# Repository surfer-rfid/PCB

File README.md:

# PCB
PCB schematics, layout, BOM, and other data required to generate the S.U.R.F.E.R. PCB.
Note that one will see "rfidr" in many places in the source code. This is short
for "RFID reader", before S.U.R.F.E.R. had a unique name.

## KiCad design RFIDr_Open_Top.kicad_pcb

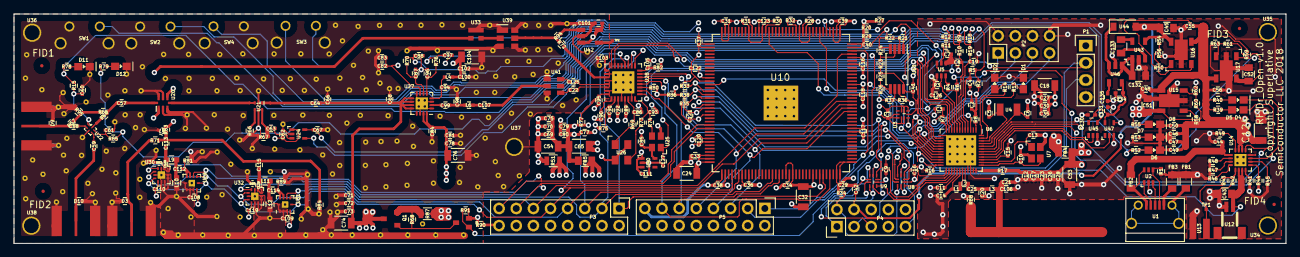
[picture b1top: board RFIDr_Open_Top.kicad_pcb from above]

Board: 4 copper layers, 188.5 x 34.0 mm, 522 parts (0 on the bottom side), 190 nets.

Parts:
C1, C2, C3, C4, C7, C8, C9, C15, C16, C17, C19, C26, C27, C29, C31, C34, C36, C38, C39, C40, C41, C42, C46, C47, C49, C50, C62, C89, C90, C92, C101, C103, C108, C109, C110, C116, C117, C118, C119, C120, C121, C122, C123, C130, C131: 100n; C_0402
C5, C6, C10, C13, C68, C86, C93: 12p; C_0402
C11: 47n; C_0402
C12, C23, C30, C33, C72, C75, C77, C78, C83, C102, C126: 1n; C_0402
C14: 2.2n; C_0402
C18, C24, C32, C53, C54, C65, C74, C76, C104, C124: 10u; C_1206
C20: 0.8p; C_0402
C21: 1.5p; C_0402
C22, C28, C35, C37, C57, C58, C59, C63, C64, C71, C79, C80, C81, C82, C100, C107, C125: 100p; C_0402
C25, C98: 2.2p; C_0402
C43, C45, C51, C52, C132, C133: 4.7u; C_0805
C44, C48, C55, C56, C85, C91, C95, C105, C111, C134: 1u; C_0402
C60, C61: 33p; C_0402
C66: 6.8p; C_0402
C67, C127: DNI; C_0402
C69, C70, C73, C135: 10n; C_0402
C84, C87, C88, C96, C97: DNP; C_0402
C94: 4.7p; C_0402
C99: 18p; C_0402
C106: 1.2p; C_0402
C112, C114: 5.2p; C_0402
C113: 15p; C_0402
C115: 20p; C_0402
C128, C129: 22p; C_0201
D1, D2, D7: LED_BLU; LED_0603
D3, D9, D10: XGD10402KR; R_0402
D4, D8, D12: LED_GRN; LED_0603
D5, D11: LED_YLW; LED_0603
D6: LED_RED; LED_0603
FB1, FB2, FB3, FB4, FB5: FERRITE; L_0805
FID1, FID2, FID3, FID4: FIDUCIAL; RFIDr_Fiducial_1mm_Dia_2.54mm_Outer_CopperTop
L1: 10n; L_0402
L2: 4.7n; L_0402
L3: 3.3n; L_0402
L4: 1n; L_0402
L5: 12n; L_0402
L6: 1.8n; L_0402
L9, L11: 3.6n; L_0603
L10, L12: 1.6n; L_0603
P1: CONN_01X04; Pin_Header_Straight_1x04
P2: CONN_02X04; Pin_Header_Straight_2x04
P3, P5: CONN_02X08; Pin_Header_Straight_2x08
P4: CONN_02X05; Pin_Header_Straight_2x05
Q1: DMP2305; SOT23
Q2: CTRL_NMOS; SOT-323
R1, R22, R37, R43, R59: DNP; R_0402
R2, R3, R5, R9, R10, R11, R12, R18, R19, R30, R31, R32, R33, R34, R35, R68, R81, R89, R91: 10k; R_0402
R4, R6: 2.2k; R_0402
R7, R8, R17, R20, R21, R27, R28, R29, R36, R41, R44, R45, R47, R50, R58, R64, R69, R70, R72, R73, R75, R76, R77, R80, R82, R86, R88, R90, R94, R95: 0; R_0402
R13, R14, R52, R53, R55: 220; R_0402
R15, R39, R40, R85: 470; R_0402
R16, R23, R25: 12k; R_0402
R24, R26: 100k; R_0402
R38: 1k; R_0402
R42: 15k; R_0402
R46: 1.13k; R_0402
R48: 46.8k; R_0402
R49: 1.1k; R_0402
R51, R87: 0; R_0805
R54: 82k; R_0402
R56: 36k; R_0402
R57, R65, R71, R74: DNI; R_0402
R60: 68k; R_0402
R61, R78, R79: 24k; R_0402
R62: 23k; R_0402
R63: 47k; R_0402
R66, R67: 50; R_0402
R83: 10; R_0402
R84: 19; R_0402
R92, R93: 10k; R_0201
SW1, SW3: SW_RESET; FSMRA3JH
SW2, SW4: SW_SAMPLE; FSMRA3JH
TP1, TP2: TESTPOINT
U1: USB_Micro_B; USB_Micro-B-Round-Pegs
U2: PUSB2X4Y; SC-70-6
U3, U8, U9: NLAS5223B; WQFN-10
U4: FC-135_32p768_XTAL; FC-135
U5: DMN63D8LDW-7; SC-70-6
U6: NRF51822; UQFN-48-1EP_6x6mm_Pitch0.4mm_wvias
U7: NX2520SA_16MHz_XTAL; NX2520
U10: 10M02E144; EQFP-144_20x20mm_Pitch0.5mm
U11: TSV358; TSSOP-8_4.4x3mm_Pitch0.65mm
U12: BatJSTCnctr; JST-SM-02B-SRSS-TB
U13: Thermocouple; THERMOCOUPLE
U14: BQ24073; QFN-16-1EP_3x3mm_Pitch0.5mm_wvias
U15, U16, U17: AP7361C-Y5-13; SOT-89-5
U18, U19, U23: SMA_72970
U20: J0910CF15B0100
U21: HHM22106
U22: SKY13350
U24: MAX2204; SC-70-5
U25: SG210STF_XO; SG210STF
U26: CX3225GB_36MHz_XTAL; CX3225
U27: SKY65111; QFN-16-1EP_3x3mm_Pitch0.5mm_wvias
U28: SX1257; QFN-32-1EP_5x5mm_Pitch0.5mm_wvias
U29, U31: PE64906; QFN-10-1EP_2x2mm_Pitch0.5mm_wvias
U30, U32: PE64102; QFN-12-1EP_2x2mm_Pitch0.5mm_wvias
U33: PAT1220
U34, U35, U36, U37, U38: MountingHole; MountingHole_2.2mm
U39: SF2049E
U40: LP5951MF; SC-70-5
U41: 0917BL18B100E
U42: LTC5505-1; TSOT-23-5
U43: LM2767M5; SOT-23-5
U44: MBR0520LTR
U45, U47: SN74LV1T34; SC-70-5
U46: LP3985IM5-5.0; SOT-23-5
V6, V7, V8, V9, V10, V11, V12, V14, V15, V16, V18, V19, V25, V35, V54, V105, V107, V108, V109, V110, V112, V113, V114, V115, V116, V117, V118, V119, V120, V121, V122, V124, V125, V126, V127, V128, V129, V130, V131, V132, V134, V135, V136, V137, V138, V139, V140, V141, V142, V143, V144, V145, V146, V147, V148, V149, V150, V151, V152, V153, V154, V155, V156, V157, V158, V159, V160, V161, V162, V163, V164, V165, V166, V167, V168, V169, V170, V171, V172, V173, V174, V175, V176, V177, V178, V179, V180, V181, V182, V183, V184, V185, V186, V187, V188, V189, V190, V191, V193, V194, V195, V196, V197, V198, V199, V200, V201, V202, V204, V205, V206, V207, V208, V209, V210, V211, V212, V213, V214, V215, V216, V217, V218, V219, V220, V221, V222, V223, V224, V225, V226, V227, V228, V229, V230, V231, V232, V234, V235, V236, V237, V312, V313, V314, V315, V316, V317, V318, V319, V320, V321, V322, V323, V324, V325, V326, V327, V328, V329, V330, V331, V332, V333, V334, V335, V336, V337, V338, V339, V340, V341, V342, V343, V344, V345, V346, V347, V348, V349, V350, V351, V357, V366, V367, V368, V369, V370, V371, V372, V373, V374, V375, V376, V377, V378, V379, V380, V381, V382, V383, V384: RF_VIA

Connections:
+1V2: C52.2, R61.2, U17.5
+2V5: C42.2, C45.2, P4.4, R54.2, U16.5, U43.4, U44.2
+5V: C130.1, C131.2, C134.1, U45.5, U46.5, U47.5
/ANT0: R15.1, R78.1, U47.4
/ANT1: R79.1, R85.2, U45.4
/CHGB: D4.1, U6.43, U14.9
/CTRLR_CIPO: P3.1, U10.54, U28.18
/CTRLR_COPI_CAP0_RDIO: P3.3, U10.52, U28.19, U32.12
/CTRLR_COPI_CAP1: P3.11, U10.105, U31.7
/CTRLR_COPI_CAP2: P3.15, U10.25, U30.12
/CTRLR_COPI_CAP3: P3.13, U10.26, U29.7
/CTRLR_NPS_DTC: P3.7, U10.40, U29.6, U30.1, U31.6, U32.1
/CTRLR_NPS_RDIO: P3.5, U10.42, U28.20
/CTRLR_PCLK: P3.9, U10.90, U28.17, U29.5, U30.3, U31.5, U32.3
/DIO2: U6.14, U28.23
/DIO3: U6.10, U28.24
/EN_VDD_1P2: R52.2, R59.1, U6.44, U17.1
/EN_VDD_PA: Q1.1, Q2.3, R68.2
/FPGA_CLK_36_IN: P5.9, U10.91, U28.10
/FPGA_IN_I: P5.5, U10.89, U28.15
/FPGA_IN_Q: P5.7, U10.88, U28.14
/FPGA_OUT_I: P5.11, U10.67, U28.13
/FPGA_OUT_Q: P5.13, U10.69, U28.12
/OPA_SPDT1_CTL: U3.8, U6.11, U24.4
/PGOODB: D5.1, U6.42, U14.7
/RDIO_RST_P: U6.15, U28.9
/RFIDr_Open_DigBB/CYCLE: R9.2, R10.2, SW4.2
/RFIDr_Open_DigBB/FPGA_IRQ: P5.1, U6.21, U10.106
/RFIDr_Open_DigBB/FPGA_PRPHL_CIPO: P2.5, U6.18, U10.115
/RFIDr_Open_DigBB/FPGA_PRPHL_COPI: P2.7, U6.17, U10.130
/RFIDr_Open_DigBB/FPGA_PRPHL_NPS: P2.3, U6.19, U10.13
/RFIDr_Open_DigBB/FPGA_PRPHL_PCLK: P2.1, U6.20, U10.113
/RFIDr_Open_DigBB/FPGA_RST_N: U6.22, U10.19
/RFIDr_Open_DigBB/FPGA_TCK_MCU: U6.28, U9.10
/RFIDr_Open_DigBB/FPGA_TDI_MCU: U6.26, U8.10
/RFIDr_Open_DigBB/FPGA_TDO_MCU: U6.25, U8.2
/RFIDr_Open_DigBB/FPGA_TMS_MCU: U6.27, U9.2
/RFIDr_Open_DigBB/PWR_TOGL: R2.2, R5.2, SW1.1
/RFIDr_Open_DigBB/RESET: R11.1, R12.1, SW3.2
/RFIDr_Open_DigBB/RFIDr_Open_FPGA/CONFIG_SEL: R28.2, U10.120
/RFIDr_Open_DigBB/RFIDr_Open_FPGA/CONF_DONE: R31.2, U10.135
/RFIDr_Open_DigBB/RFIDr_Open_FPGA/FPGA_TCK: R38.1, U9.9, U10.16
/RFIDr_Open_DigBB/RFIDr_Open_FPGA/FPGA_TDI: R35.2, U8.9, U10.17
/RFIDr_Open_DigBB/RFIDr_Open_FPGA/FPGA_TDO: U8.3, U10.18
/RFIDr_Open_DigBB/RFIDr_Open_FPGA/FPGA_TMS: R33.2, U9.3, U10.15
/RFIDr_Open_DigBB/RFIDr_Open_FPGA/JTAG_SEL: P4.2, R34.2, U8.4, U8.8, U9.4, U9.8
/RFIDr_Open_DigBB/RFIDr_Open_FPGA/JTAG_TCK: P4.1, U9.7
/RFIDr_Open_DigBB/RFIDr_Open_FPGA/JTAG_TDI: P4.9, U8.7
/RFIDr_Open_DigBB/RFIDr_Open_FPGA/JTAG_TDO: P4.3, U8.5
/RFIDr_Open_DigBB/RFIDr_Open_FPGA/JTAG_TMS: P4.5, U9.5
/RFIDr_Open_DigBB/RFIDr_Open_FPGA/NCONFIG: R32.2, U10.122
/RFIDr_Open_DigBB/RFIDr_Open_FPGA/NSTATUS: R30.2, U10.131
/RFIDr_Open_DigBB/RFIDr_Open_MCU/ADC_IN: R4.1, R6.2, U6.7
/RFIDr_Open_DigBB/RFIDr_Open_MCU/ANT0_3V: U6.40, U47.2
/RFIDr_Open_DigBB/RFIDr_Open_MCU/ANT1B: L1.1, L2.1, U6.31
/RFIDr_Open_DigBB/RFIDr_Open_MCU/ANT1_3V: U6.41, U45.2
/RFIDr_Open_DigBB/RFIDr_Open_MCU/ANT2B: C25.1, L2.2, U6.32
/RFIDr_Open_DigBB/RFIDr_Open_MCU/BAT_LED0: R14.2, U6.48
/RFIDr_Open_DigBB/RFIDr_Open_MCU/BAT_LED1: R13.2, U6.47
/RFIDr_Open_DigBB/RFIDr_Open_MCU/BAT_SENSE: R3.2, U5.2, U6.8
/RFIDr_Open_DigBB/RFIDr_Open_MCU/BTLE_DECOUPLE1: C15.1, U6.39
/RFIDr_Open_DigBB/RFIDr_Open_MCU/BTLE_DECOUPLE2: C11.1, U6.29
/RFIDr_Open_DigBB/RFIDr_Open_MCU/BTLE_SWCLK: P1.3, R16.2, U6.24
/RFIDr_Open_DigBB/RFIDr_Open_MCU/BTLE_SWDIO: P1.2, U5.6, U6.23
/RFIDr_Open_DigBB/RFIDr_Open_MCU/CYCLE_F: C8.2, R10.1, U6.6
/RFIDr_Open_DigBB/RFIDr_Open_MCU/LPXC1_BT: C6.1, U4.2, U6.45
/RFIDr_Open_DigBB/RFIDr_Open_MCU/LPXC2_BT: C5.1, U4.1, U6.46
/RFIDr_Open_DigBB/RFIDr_Open_MCU/PWR_TOGL_F: C4.2, R5.1, U6.4
/RFIDr_Open_DigBB/RFIDr_Open_MCU/RESET_F: C7.2, R11.2, U5.5
/RFIDr_Open_DigBB/RFIDr_Open_MCU/RFIDr_Open_BTLE_ANT/ANT: C21.1, C106.1, L3.2, R88.1
/RFIDr_Open_DigBB/RFIDr_Open_MCU/RFIDr_Open_PA_BIAS_CTRL/DAC_OA0: R23.1, R24.1, U11.3
/RFIDr_Open_DigBB/RFIDr_Open_MCU/RFIDr_Open_PA_BIAS_CTRL/DAC_OA0_FB: R21.1, R22.1, U11.2
/RFIDr_Open_DigBB/RFIDr_Open_MCU/RFIDr_Open_PA_BIAS_CTRL/DAC_OA1: R25.1, R26.1, U11.5
/RFIDr_Open_DigBB/RFIDr_Open_MCU/RFIDr_Open_PA_BIAS_CTRL/DAC_OA1_FB: R36.1, R37.1, U11.6
/RFIDr_Open_DigBB/RFIDr_Open_MCU/RFIDr_Open_PA_BIAS_CTRL/VDD_OPA_PA: C41.1, R23.2, R25.2, U3.9, U11.8
/RFIDr_Open_DigBB/RFIDr_Open_MCU/SAMPLE_F: C19.2, R19.1, U6.5
/RFIDr_Open_DigBB/RFIDr_Open_MCU/VDD_PA_BTLE: C14.1, L1.2, U6.30
/RFIDr_Open_DigBB/RFIDr_Open_MCU/XC1_BT: C10.1, U6.37, U7.3
/RFIDr_Open_DigBB/RFIDr_Open_MCU/XC2_BT: C13.1, U6.38, U7.1
/RFIDr_Open_DigBB/SAMPLE: R18.2, R19.2, SW2.1
/RFIDr_Open_PMU/ID: R1.2, U1.4, U2.4
/RFIDr_Open_PMU/RFIDr_Open_LDOS_QPUMP/CP_M: C133.2, U43.3
/RFIDr_Open_PMU/RFIDr_Open_LDOS_QPUMP/CP_P: C133.1, U43.5
/RFIDr_Open_PMU/RFIDr_Open_LDOS_QPUMP/VFB_1P2: R61.1, R63.2, U17.3
/RFIDr_Open_PMU/RFIDr_Open_LDOS_QPUMP/VFB_2P5: R54.1, R56.2, U16.3
/RFIDr_Open_PMU/RFIDr_Open_LDOS_QPUMP/VFB_3V: R60.1, R62.2, U15.3
/RFIDr_Open_PMU/RFIDr_Open_PMU_CORE/CEB: R41.1, U14.4
/RFIDr_Open_PMU/RFIDr_Open_PMU_CORE/ILIM: R49.1, U14.12
/RFIDr_Open_PMU/RFIDr_Open_PMU_CORE/ISET: R46.1, U14.16
/RFIDr_Open_PMU/RFIDr_Open_PMU_CORE/TD: R47.1, U14.15
/RFIDr_Open_PMU/RFIDr_Open_PMU_CORE/THERMOCOUPLE: R43.1, TP1.1, U13.1
/RFIDr_Open_PMU/RFIDr_Open_PMU_CORE/TMR: R48.1, U14.14
/RFIDr_Open_PMU/RFIDr_Open_PMU_CORE/TS: R42.2, R43.2, U14.1
/RFIDr_Open_PMU/USB_DM: U1.2, U2.1
/RFIDr_Open_PMU/USB_DP: U1.3, U2.3
/RFIDr_Open_PMU/USB_VBUS: C44.2, FB2.2, U14.13
/RFIDr_Open_PMU/USB_VBUS_PRE: FB2.1, U1.1, U2.6
/RFIDr_Open_Radio/RFIDr_Open_ANT_ACCESS/RX_ANT: U20.1, U33.2
/RFIDr_Open_Radio/RFIDr_Open_ANT_ACCESS/RX_ATT: U33.1, U39.2
/RFIDr_Open_Radio/RFIDr_Open_ANT_ACCESS/RX_FILT: R72.2, R94.1, U39.5
/RFIDr_Open_Radio/RFIDr_Open_ANT_ACCESS/TX_ANT: C57.1, U20.8
/RFIDr_Open_Radio/RFIDr_Open_PA/PA_FILT_OUT: C64.1, U21.1
/RFIDr_Open_Radio/RFIDr_Open_PA/PA_IN: C107.2, L6.1
/RFIDr_Open_Radio/RFIDr_Open_PA/PA_OUT: U20.4, U21.3
/RFIDr_Open_Radio/RFIDr_Open_TRX/RF2: C107.1, U41.2
/RFIDr_Open_Radio/RFIDr_Open_TRX/RF_ON: C125.2, U28.29
/RFIDr_Open_Radio/RFIDr_Open_TRX/RF_OP: C22.2, U28.30
/RFIDr_Open_Radio/RFIDr_Open_TRX/V1P8: C85.2, U25.4, U40.5
/RFIDr_Open_Radio/TERM: R83.2, U20.5
/RFPA_VCA: C88.1, R21.2, R70.1, U11.1
/RFPA_VCB: C97.1, R36.2, R76.1, U11.7
/RSSI_DET: C67.2, C126.2, P5.3, U6.9, U24.5
/VBAT: C43.2, R6.1, U12.1, U14.2, U14.3
/XO_ENABLE: C127.2, U6.16, U25.1
GND: C1.1, C2.1, C3.1, C4.1, C5.2, C6.2, C7.1, C8.1, C9.2, C10.2, C11.2, C12.2, C13.2, C14.2, C15.2, C16.2, C17.2, C18.2, C19.1, C20.2, C21.2, C23.2, C24.2, C26.2, C27.2, C28.2, C29.2, C30.2, C31.2, C32.2, C33.2, C34.2, C35.2, C36.2, C37.2, C38.2, C39.2, C40.2, C41.2, C42.1, C43.1, C44.1, C45.1, C46.1, C47.1, C48.2, C49.1, C50.1, C51.1, C52.1, C53.2, C55.2, C56.2, C106.2, C116.2, C117.2, C118.2, C120.2, C121.2, C122.2, C123.2, C124.2, C126.1, C130.2, C131.1, C132.1, C134.2, C135.2, D1.1, D2.1, D6.1, D7.1, D8.1, FB1.1, FB3.1, P1.4, P2.2, P2.4, P2.6, P2.8, P3.2, P3.4, P3.6, P3.8, P3.10, P3.12, P3.14, P3.16, P4.10, P5.2, P5.4, P5.6, P5.8, P5.10, P5.12, P5.14, P5.16, R1.1, R3.1, R12.2, R16.1, R22.2, R24.2, R26.2, R28.1, R37.2, R38.2, R41.2, R42.1, R45.2, R46.2, R47.2, R48.2, R49.2, R51.2, R53.2, R56.1, R62.1, R63.1, R86.2, R88.2, R90.2, U2.2, U3.4, U3.5, U3.6, U3.7, U5.1, U5.4, U6.13, U6.33, U6.34, U6.49, U7.2, U7.4, U8.6, U9.6, U10.11, U10.20, U10.30, U10.38, U10.45, U10.57, U10.66, U10.83, U10.96, U10.104, U10.110, U10.119, U10.133, U10.143, U10.145, U11.4, U12.2, U13.2, U14.8, U14.17, U15.2, U16.2, U17.2, U34.1, U35.1, U43.2, U45.3, U46.2, U47.3
GNDA: C54.2, C60.2, C61.1, C62.2, C65.2, C66.1, C67.1, C68.1, C69.2, C70.2, C71.1, C72.1, C73.1, C74.1, C75.2, C76.2, C77.2, C78.2, C79.2, C80.2, C81.2, C82.1, C83.1, C84.2, C85.1, C86.1, C87.2, C88.2, C89.2, C90.2, C91.1, C92.2, C93.1, C94.2, C95.2, C96.2, C97.2, C98.1, C100.2, C101.2, C102.2, C103.2, C104.2, C105.1, C108.2, C109.2, C110.2, C111.2, C119.2, C127.1, D3.2, D9.1, D10.2, D11.1, D12.1, L5.2, L10.2, L12.2, Q2.2, R51.1, R66.1, R67.1, R80.1, R81.1, R84.2, R86.1, R89.1, R90.1, R91.1, R92.2, R93.2, R95.2, SW1.2, SW1.3, SW2.2, SW2.3, SW3.3, SW4.1, SW4.3, U18.0, U18.2, U18.3, U18.4, U19.0, U19.2, U19.3, U19.4, U20.2, U20.3, U20.6, U20.7, U21.2, U21.5, U22.3, U23.0, U23.2, U23.3, U23.4, U24.2, U25.2, U26.2, U26.4, U27.1, U27.3, U27.8, U27.14, U27.17, U28.4, U28.7, U28.26, U28.28, U28.31, U28.33, U29.1, U29.2, U29.3, U29.10, U29.11, U30.2, U30.5, U30.6, U30.7, U30.8, U30.11, U30.13, U31.1, U31.2, U31.3, U31.10, U31.11, U32.2, U32.5, U32.6, U32.7, U32.8, U32.11, U32.13, U33.3, U36.1, U37.1, U38.1, U39.1, U39.3, U39.4, U39.6, U40.2, U41.1, U41.3, U42.2, V6.1, V7.1, V8.1, V9.1, V10.1, V11.1, V12.1, V14.1, V15.1, V16.1, V18.1, V19.1, V25.1, V35.1, V54.1, V105.1, V107.1, V108.1, V109.1, V110.1, V112.1, V113.1, V114.1, V115.1, V116.1, V117.1, V118.1, V119.1, V120.1, V121.1, V122.1, V124.1, V125.1, V126.1, V127.1, V128.1, V129.1, V130.1, V131.1, V132.1, V134.1, V135.1, V136.1, V137.1, V138.1, V139.1, V140.1, V141.1, V142.1, V143.1, V144.1, V145.1, V146.1, V147.1, V148.1, V149.1, V150.1, V151.1, V152.1, V153.1, V154.1, V155.1, V156.1, V157.1, V158.1, V159.1, V160.1, V161.1, V162.1, V163.1, V164.1, V165.1, V166.1, V167.1, V168.1, V169.1, V170.1, V171.1, V172.1, V173.1, V174.1, V175.1, V176.1, V177.1, V178.1, V179.1, V180.1, V181.1, V182.1, V183.1, V184.1, V185.1, V186.1, V187.1, V188.1, V189.1, V190.1, V191.1, V193.1, V194.1, V195.1, V196.1, V197.1, V198.1, V199.1, V200.1, V201.1, V202.1, V204.1, V205.1, V206.1, V207.1, V208.1, V209.1, V210.1, V211.1, V212.1, V213.1, V214.1, V215.1, V216.1, V217.1, V218.1, V219.1, V220.1, V221.1, V222.1, V223.1, V224.1, V225.1, V226.1, V227.1, V228.1, V229.1, V230.1, V231.1, V232.1, V234.1, V235.1, V236.1, V237.1, V312.1, V313.1, V314.1, V315.1, V316.1, V317.1, V318.1, V319.1, V320.1, V321.1, V322.1, V323.1, V324.1, V325.1, V326.1, V327.1, V328.1, V329.1, V330.1, V331.1, V332.1, V333.1, V334.1, V335.1, V336.1, V337.1, V338.1, V339.1, V340.1, V341.1, V342.1, V343.1, V344.1, V345.1, V346.1, V347.1, V348.1, V349.1, V350.1, V351.1, V357.1, V366.1, V367.1, V368.1, V369.1, V370.1, V371.1, V372.1, V373.1, V374.1, V375.1, V376.1, V377.1, V378.1, V379.1, V380.1, V381.1, V382.1, V383.1, V384.1
unnamed: C20.1, C25.2, L3.1
unnamed: C22.1, U41.4
unnamed: C57.2, R64.2, R65.1
unnamed: C58.1, U22.2
unnamed: C58.2, D9.2, R57.1, U18.1
unnamed: C59.1, U22.4
unnamed: C59.2, D10.1, U19.1
unnamed: C60.1, R15.2, U22.1
unnamed: C61.2, R85.1, U22.5
unnamed: C63.1, R67.2, U21.6
unnamed: C63.2, U24.3
unnamed: C86.2, R69.2, U28.6
unnamed: C87.1, R70.2, U27.6
unnamed: C89.1, U28.5
unnamed: C90.1, U28.1
unnamed: C91.2, R75.2, U28.2
unnamed: C92.1, U28.3
unnamed: C93.2, R73.2, R74.2, U28.8
unnamed: C94.1, L4.2, U27.4
unnamed: C95.1, R77.1, U28.32
unnamed: C96.1, R76.2, U27.5
unnamed: C98.2, C99.2, L6.2
unnamed: C99.1, U27.2
unnamed: C103.1, U28.25
unnamed: C105.2, R82.1, U28.16
unnamed: C112.1, L9.2, L10.1
unnamed: C112.2, R81.2, U29.8, U29.9
unnamed: C113.1, C115.1, L5.1, R71.1, R83.1, R84.1
unnamed: C113.2, C128.1, L9.1
unnamed: C114.1, L11.2, L12.1
unnamed: C114.2, R89.2, U31.8, U31.9
unnamed: C115.2, C129.1, L11.1
unnamed: C125.1, U41.6
unnamed: C128.2, R92.1, U30.9, U30.10
unnamed: C129.2, R93.1, U32.9, U32.10
unnamed: C132.2, U43.1, U44.1, U46.1, U46.3
unnamed: C135.1, U46.4
unnamed: D1.2, R13.1
unnamed: D2.2, R14.1
unnamed: D3.1, R71.2, U23.1
unnamed: D4.2, R39.1
unnamed: D5.2, R40.1
unnamed: D6.2, R52.1
unnamed: D7.2, R53.1
unnamed: D8.2, R55.1
unnamed: D11.2, R78.2
unnamed: D12.2, R79.2
unnamed: FB1.2, U1.6
unnamed: FB3.2, U1.5
unnamed: Q1.2, R68.1, R87.2
unnamed: Q2.1, R91.2, U6.3
unnamed: R4.2, U5.3
unnamed: R7.1, U6.12
unnamed: R8.2, U6.1
unnamed: R17.1, U6.35, U6.36
unnamed: R44.1, U14.5
unnamed: R45.1, U14.6
unnamed: R50.1, U16.1
unnamed: R57.2, R65.2, R95.1
unnamed: R58.1, U15.1
unnamed: R64.1, U22.6
unnamed: R66.2, U21.4
unnamed: R69.1, U26.1
unnamed: R72.1, U28.27
unnamed: R73.1, U26.3
unnamed: R74.1, U25.3
unnamed: R80.2, U28.11
unnamed: R94.2, U42.1
unnamed: TP2.1, U42.4
VAA: C54.1, C62.1, C65.1, C69.1, C70.1, C75.1, C77.1, C79.1, C80.1, C101.1, C108.1, C109.1, C110.1, C111.1, C119.1, FB5.2, R75.1, R77.2, R82.2, U24.1, U29.4, U30.4, U31.4, U32.4, U40.1, U40.3, U42.3, U42.5
VCC: C46.2, C47.2, C48.1, C49.2, C50.2, C55.1, C56.1, C124.1, R39.2, R40.2, R44.2, R50.2, R58.2, R59.2, R87.1, U14.10, U14.11, U15.4, U16.4, U17.4
VDD: C1.2, C2.2, C3.2, C9.1, C16.1, C18.1, C24.1, C27.1, C29.1, C30.1, C31.1, C32.1, C33.1, C34.1, C35.1, C36.1, C37.1, C38.1, C39.1, C40.1, C51.2, C116.1, C117.1, C118.1, C120.1, C121.1, C122.1, C123.1, FB4.1, FB5.1, P1.1, P5.15, R2.1, R7.2, R8.1, R9.1, R18.1, R20.1, R27.2, R29.1, R29.2, R30.1, R31.1, R32.1, R33.1, R34.1, R35.1, R55.2, R60.2, SW3.1, U3.1, U3.2, U3.10, U8.1, U9.1, U10.1, U10.2, U10.12, U10.22, U10.29, U10.34, U10.35, U10.36, U10.37, U10.43, U10.56, U10.58, U10.64, U10.71, U10.72, U10.73, U10.82, U10.93, U10.102, U10.107, U10.108, U10.109, U10.111, U10.118, U10.121, U10.132, U10.136, U10.142, U10.144, U15.5
VPP: C64.2, C66.2, C68.2, C71.2, C72.2, C73.2, C74.2, C76.1, C78.1, C81.1, C82.2, C83.2, C84.1, C100.1, C102.1, C104.1, L4.1, Q1.3, U27.7, U27.9, U27.10, U27.11, U27.12, U27.15, U27.16
VSS: C12.1, C17.1, C23.1, C26.1, C28.1, C53.1, FB4.2, R17.2

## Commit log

2021-01-26 Push Kicad files to repo for first time.
    Push kicad files to repo for first time.
2021-01-27 Update RFIDr_Open_BOM.xls
    Fixed BOM - somehow designators had been cut off. Also, hand-edited the changes required to get the transmit I/Q DAC offset calibration working.
2021-01-30 Add missing footprint, fp-lib-table.
    Add some files to the main PCB repo.
2024-04-08 DNI C67 In Schematics and Layout
    C67 was DNIed in the BOM but not in the schematics/layout. C67 needs to be DNI or a small value for the SX1257 DAC autocalibration procedure to work. We DNIed C67 in both the schematic and layout to 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
2024-11-30 Change value of C126 to 1nF.
    In order for the DAC autocalibration routine to work, C67 needs to be DNI and C126 needs to be 1nF. Previously this had been changed in the BOM but not in the schematic or PCB. We fix this here.

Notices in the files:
RFIDr_Open_Top.kicad_pcb:
Licensed under CERN-OHL-P v2 or later.
Copyright 2021 Superlative Semiconductor LLC.
Copyright Superlative
